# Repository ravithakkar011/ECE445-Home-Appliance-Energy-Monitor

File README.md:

# ECE445-Home-Appliance-Energy-Monitor

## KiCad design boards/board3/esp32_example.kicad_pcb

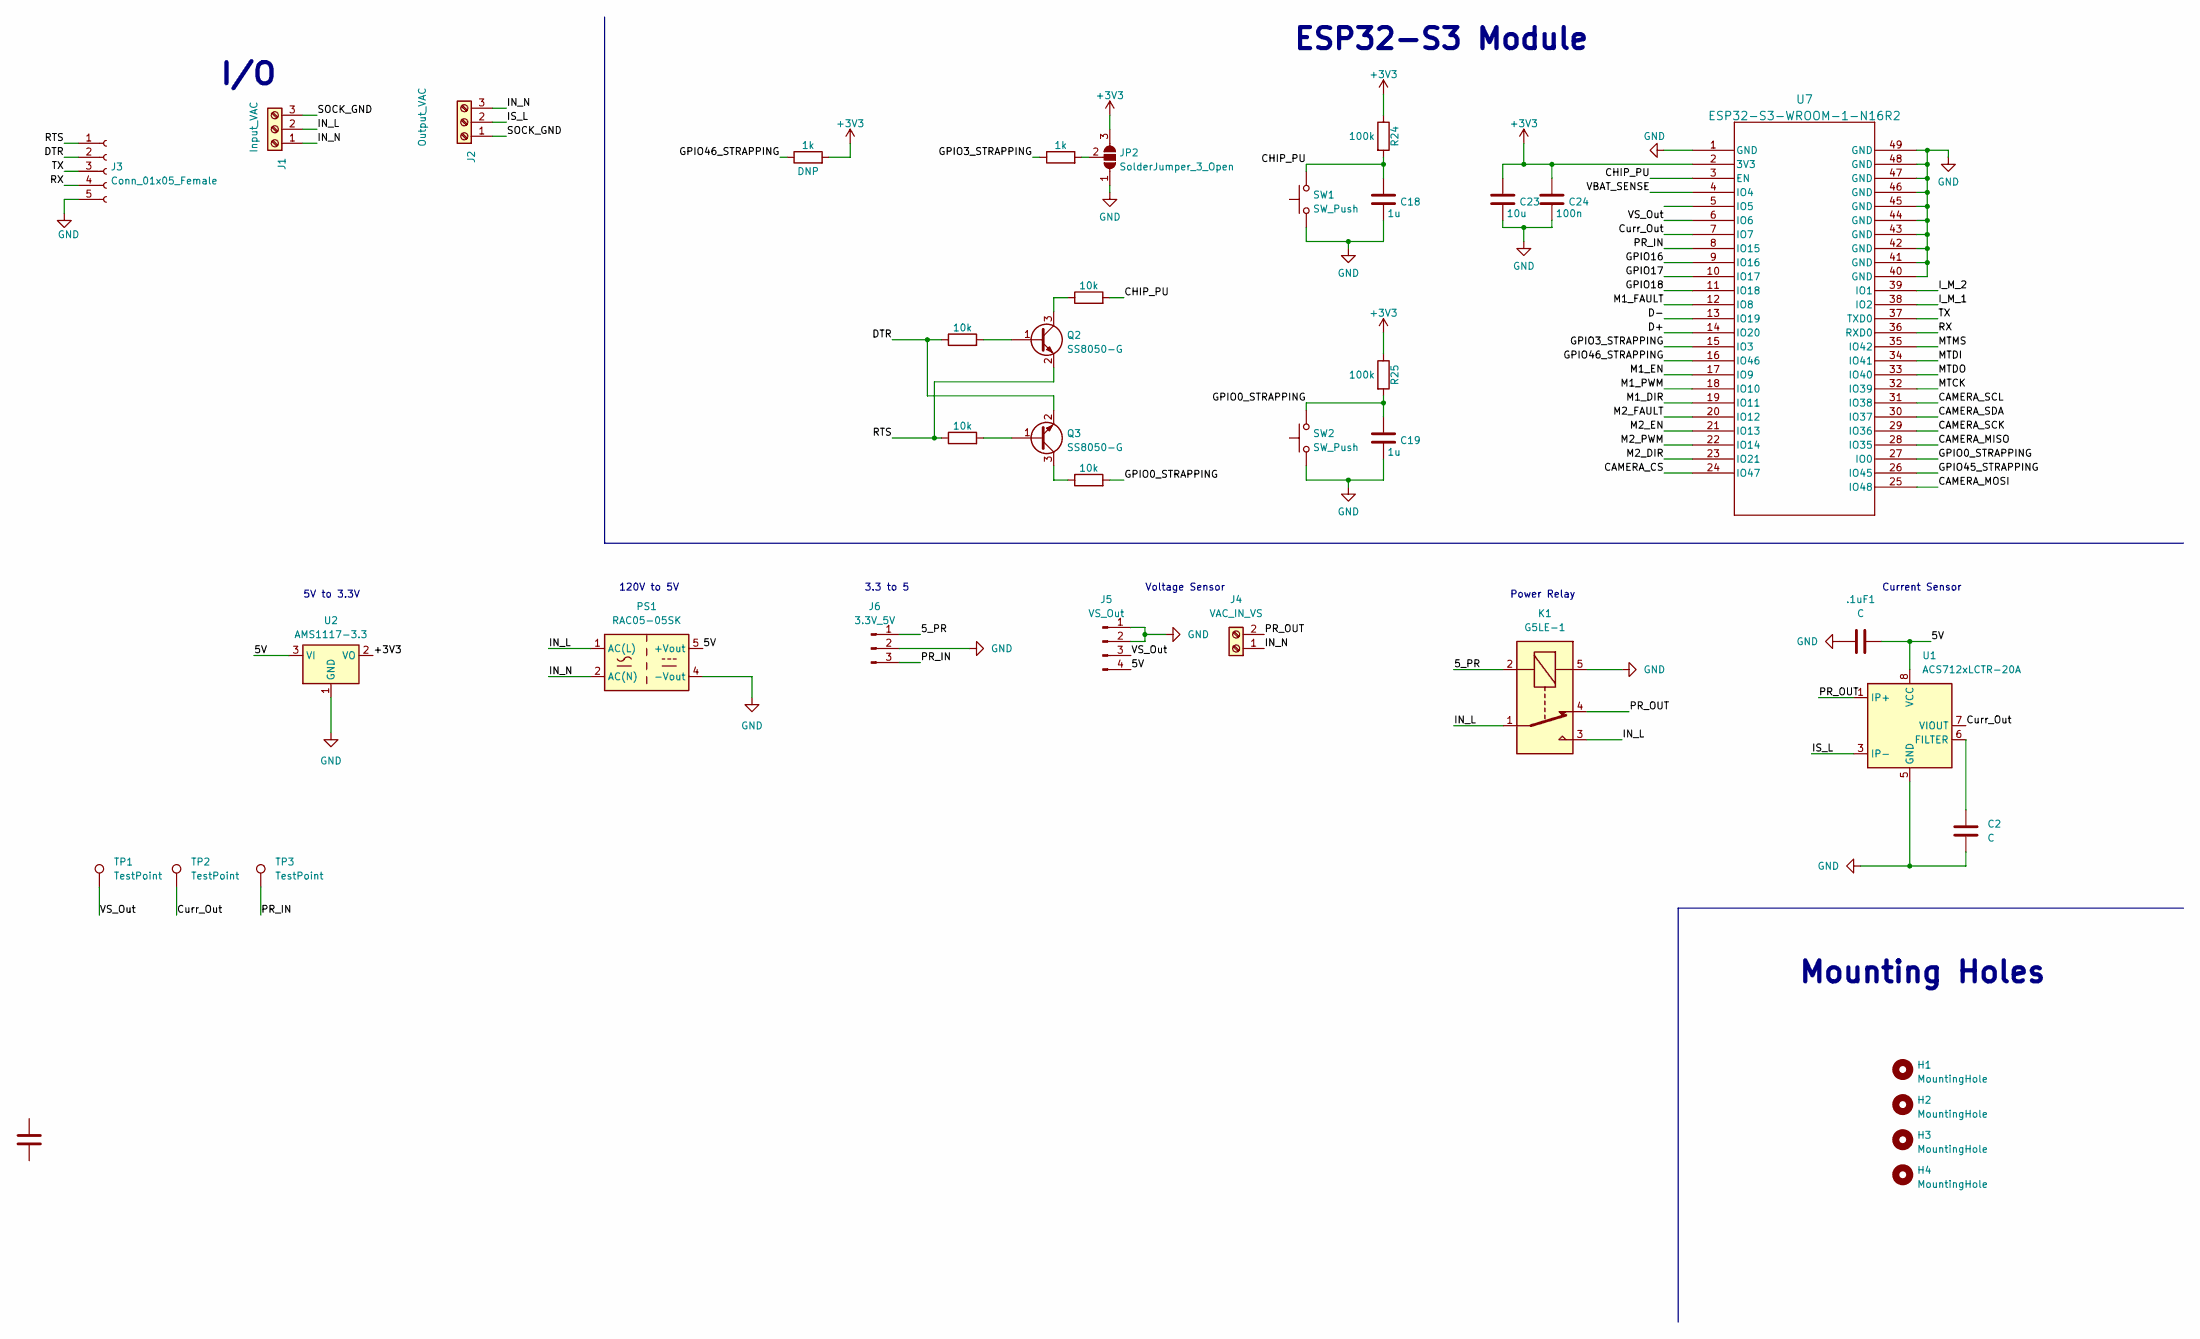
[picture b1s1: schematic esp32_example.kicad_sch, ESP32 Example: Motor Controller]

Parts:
.1uF1: C; C_0201_0603Metric
C1: 10u; R_1206_3216Metric
C2: C; C_0201_0603Metric
C18, C19: 1u; C_0805_2012Metric
C23: 10u; C_0805_2012Metric
C24: 100n; C_0805_2012Metric
H1, H2, H3, H4: MountingHole; MountingHole_3.2mm_M3
J1: Input_VAC; TerminalBlock_Phoenix_MKDS-1,5-3-5.08_1x03_P5.08mm_Horizont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
J2: Output_VAC; TerminalBlock_Phoenix_MKDS-1,5-3-5.08_1x03_P5.08mm_Horizont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
J3: Conn_01x05_Female; PinHeader_1x05_P2.54mm_Vertical
J4: VAC_IN_VS; TerminalBlock_Phoenix_MKDS-1,5-2_1x02_P5.00mm_Horizontal
J5: VS_Out; Molex_KK-254_AE-6410-04A_1x04_P2.54mm_Vertical
J6: 3.3V_5V; Molex_KK-254_AE-6410-03A_1x03_P2.54mm_Vertical
JP2: SolderJumper_3_Open; SolderJumper-3_P2.0mm_Open_TrianglePad1.0x1.5mm
K1: G5LE-1; Relay_SPDT_Omron-G5LE-1
PS1: RAC05-05SK; Converter_ACDC_RECOM_RAC05-xxSK_THT
Q2, Q3: SS8050-G; SOT-23
R12, R17: 1k; R_0805_2012Metric
R13, R14, R18, R19: 10k; R_0805_2012Metric
R24, R25: 100k; R_0805_2012Metric
SW1, SW2: SW_Push; SW_SPST_B3S-1000
TP1, TP2, TP3: TestPoint; TestPoint_Keystone_5010-5014_Multipurpose
U1: ACS712xLCTR-20A; SOIC-8_3.9x4.9mm_P1.27mm
U2: AMS1117-3.3; SOT-223-3_TabPin2
U7: ESP32-S3-WROOM-1-N16R2; ESP32-S3-WROOM-1_EXP

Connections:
+3V3: C23.1, C24.1, JP2.3 (B), R12.2, R24.1, R25.1, U2.2 (VO), U7.2 (3V3)
/5V: .1uF1.2, J5.4, PS1.5 (+Vout), U1.8 (VCC), U2.3 (VI)
/5_PR: J6.1, K1.2
/CAMERA_CS: U7.24 (IO47)
/CAMERA_MISO: U7.28 (IO35)
/CAMERA_MOSI: U7.25 (IO48)
/CAMERA_SCK: U7.29 (IO36)
/CAMERA_SCL: U7.31 (IO38)
/CAMERA_SDA: U7.30 (IO37)
/CHIP_PU: C18.1, R18.2, R24.2, SW1.2, U7.3 (EN)
/Curr_Out: TP2.1, U1.7 (VIOUT), U7.7 (IO7)
/D+: U7.14 (IO20)
/D-: U7.13 (IO19)
/DTR: J3.2, Q3.2 (E), R13.1
/GPIO0_STRAPPING: C19.1, R19.2, R25.2, SW2.2, U7.27 (IO0)
/GPIO3_STRAPPING: R17.1, U7.15 (IO3)
/GPIO16: U7.9 (IO16)
/GPIO17: U7.10 (IO17)
/GPIO18: U7.11 (IO18)
/GPIO45_STRAPPING: U7.26 (IO45)
/GPIO46_STRAPPING: R12.1, U7.16 (IO46)
/IN_L: J1.2, K1.1, K1.3, PS1.1 (AC(L))
/IN_N: J1.1, J2.3, J4.1, PS1.2 (AC(N))
/IS_L: J2.2, U1.3 (IP-), U1.4 (IP-)
/I_M_1: U7.38 (IO2)
/I_M_2: U7.39 (IO1)
/M1_DIR: U7.19 (IO11)
/M1_EN: U7.17 (IO9)
/M1_FAULT: U7.12 (IO8)
/M1_PWM: U7.18 (IO10)
/M2_DIR: U7.23 (IO21)
/M2_EN: U7.21 (IO13)
/M2_FAULT: U7.20 (IO12)
/M2_PWM: U7.22 (IO14)
/MTCK: U7.32 (IO39)
/MTDI: U7.34 (IO41)
/MTDO: U7.33 (IO40)
/MTMS: U7.35 (IO42)
/PR_IN: J6.3, TP3.1, U7.8 (IO15)
/PR_OUT: J4.2, K1.4, U1.1 (IP+), U1.2 (IP+)
/RTS: J3.1, Q2.2 (E), R14.1
/RX: J3.4, U7.36 (RXD0)
/SOCK_GND: J1.3, J2.1
/TX: J3.3, U7.37 (TXD0)
/VBAT_SENSE: U7.4 (IO4)
/VS_Out: J5.3, TP1.1, U7.6 (IO6)
GND: .1uF1.1, C2.2, C18.2, C19.2, C23.2, C24.2, J3.5, J5.1, J5.2, J6.2, JP2.1 (A), K1.5, PS1.4 (-Vout), SW1.1, SW2.1, U1.5 (GND), U2.1 (GND), U7.1 (GND), U7.40 (GND), U7.41 (GND), U7.42 (GND), U7.43 (GND), U7.44 (GND), U7.45 (GND), U7.46 (GND), U7.47 (GND), U7.48 (GND), U7.49 (GND)
unnamed: JP2.2 (C), R17.2
unnamed: Q2.1 (B), R13.2
unnamed: Q2.3 (C), R18.1
unnamed: Q3.1 (B), R14.2
unnamed: Q3.3 (C), R19.1
unnamed: C2.1, U1.6 (FILTER)

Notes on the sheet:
Voltage Sensor
3.3 to 5
Current Sensor
120V to 5V
ESP32-S3 Module
Mounting Holes
5V to 3.3V
Power Relay
I/O

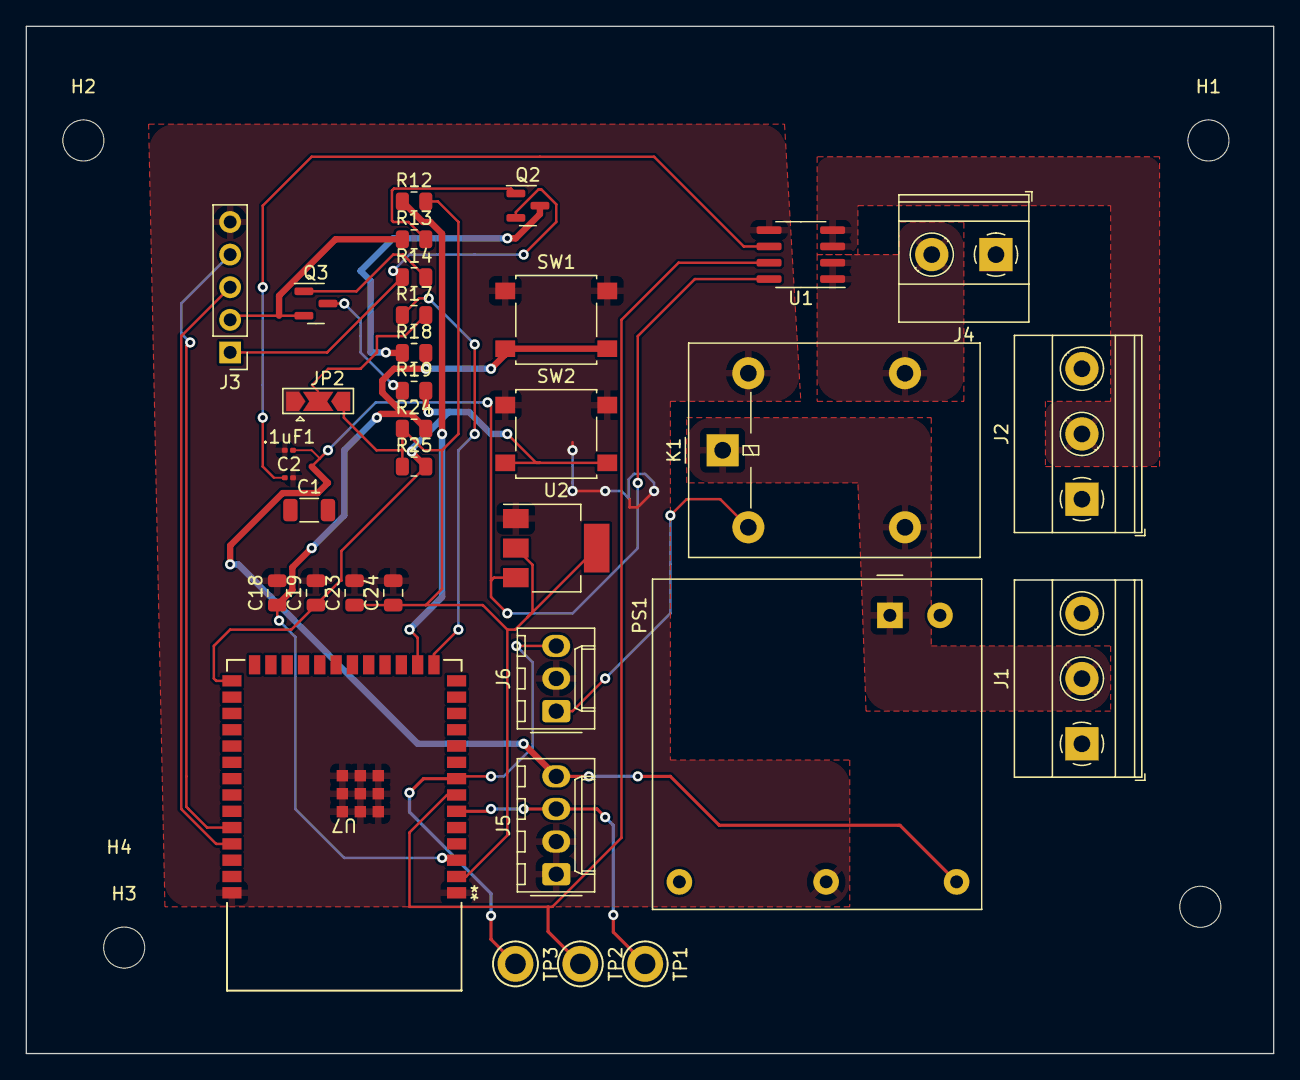
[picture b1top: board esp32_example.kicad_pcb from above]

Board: 2 copper layers, 97.2 x 80.0 mm, 38 parts (0 on the bottom side), 26 nets.

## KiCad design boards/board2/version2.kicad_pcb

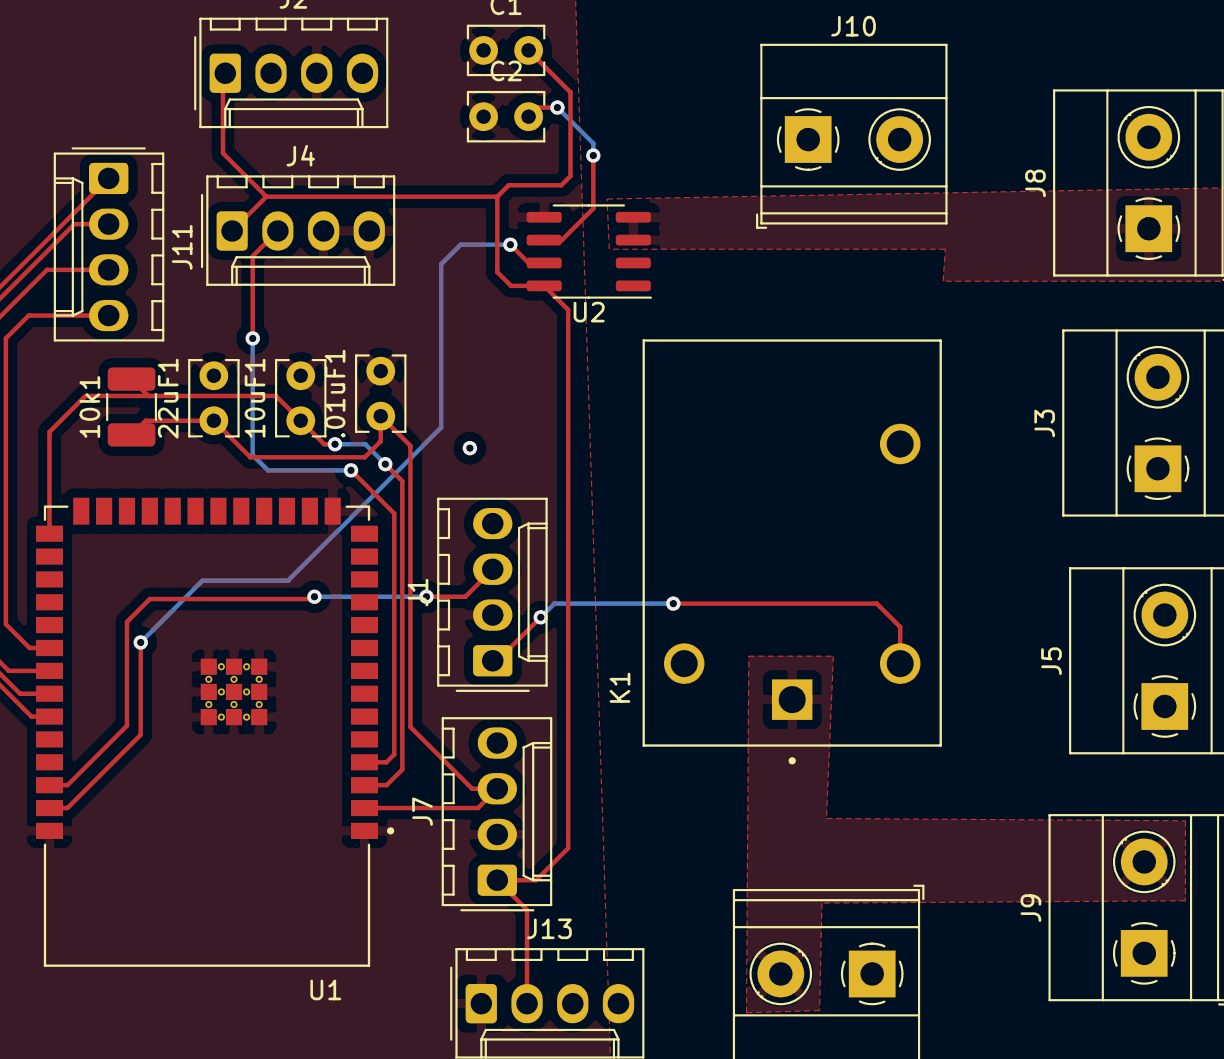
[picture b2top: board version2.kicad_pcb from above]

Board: 2 copper layers, 21 parts (0 on the bottom side), 18 nets.

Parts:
10k1: R; R_1210_3225Metric_Pad1.30x2.65mm_HandSolder
10uF1, 22uF1, .01uF1: C; C_Rect_L4.0mm_W2.5mm_P2.50mm
C1, C2: C; C_Rect_L4.0mm_W2.5mm_P2.50mm
J1: 3.3_5_boost; Molex_KK-254_AE-6410-04A_1x04_P2.54mm_Vertical
J2: Scopy Connection; Molex_KK-254_AE-6410-04A_1x04_P2.54mm_Vertical
J3: SecondOutGND; TerminalBlock_Phoenix_MKDS-1,5-2-5.08_1x02_P5.08mm_Horizont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
J4: Voltage_Sensor; Molex_KK-254_AE-6410-04A_1x04_P2.54mm_Vertical
J5: SecondGNDPin; TerminalBlock_Phoenix_MKDS-1,5-2-5.08_1x02_P5.08mm_Horizont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
J7: 5_3_connector; Molex_KK-254_AE-6410-04A_1x04_P2.54mm_Vertical
J8: OutVAC; TerminalBlock_Phoenix_MKDS-1,5-2-5.08_1x02_P5.08mm_Horizont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
J9: MainPin; TerminalBlock_Phoenix_MKDS-1,5-2-5.08_1x02_P5.08mm_Horizont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
J10: Voltage_Sensor_Input; TerminalBlock_Phoenix_MKDS-1,5-2-5.08_1x02_P5.08mm_Horizont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
J11: JTAG; Molex_KK-254_AE-6410-04A_1x04_P2.54mm_Vertical
J13: OutPut and Ground; Molex_KK-254_AE-6410-04A_1x04_P2.54mm_Vertical
J14: VAC Conn; TerminalBlock_Phoenix_MKDS-1,5-2-5.08_1x02_P5.08mm_Horizont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
K1: G5LE-1A; RELAY_G5LE-1A-EDC5
U1: ESP32-S3-WROOM-1-N16R2; XCVR_ESP32-S3-WROOM-1-N16R2
U2: ACS712xLCTR-20A; SOIC-8_3.9x4.9mm_P1.27mm

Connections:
GND: 10uF1.2, 22uF1.2, .01uF1.2, C1.1, C2.1, J1.2, J2.3, J4.3, J4.4, J7.2, J13.1, K1.5, U1.1, U1.15, U1.40, U1.41_1, U1.41_2, U1.41_3, U1.41_4, U1.41_5, U1.41_6, U1.41_7, U1.41_8, U1.41_9, U2.5
unnamed: 10k1.2, 10uF1.1, U1.3, U1.27
unnamed: 10k1.1, 22uF1.1, .01uF1.1, J7.3, U1.2
unnamed: C1.2, J2.1, J4.1, J7.1, J13.2, U2.8
unnamed: C2.2, U2.6
unnamed: J1.1, K1.2
unnamed: J1.3, U1.38
unnamed: J3.2, J5.1
unnamed: J4.2, U1.4
unnamed: J8.1, U2.3, U2.4
unnamed: J10.1, K1.3, U2.1, U2.2
unnamed: J8.2, J9.1, J10.2, J14.1
unnamed: J11.1, U1.35
unnamed: J11.2, U1.34
unnamed: J11.3, U1.33
unnamed: J11.4, U1.32
unnamed: J9.2, J14.2, K1.1
unnamed: U1.39, U2.7

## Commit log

2023-09-12 added directories and readmes
2023-10-25 PCB design 2
2023-11-29 working copy of the esp controller application
2023-12-07 Create 8-28-23 Team Meeting
2023-12-07 Create 8-31-23
2023-12-07 Rename 8-31-23 to 8-31-23 Team Meeting
2023-12-07 Create 9-5-23 Team Meeting
2023-12-07 Create 9-12-23 Team Meeting
2023-12-07 Rename 8-28-23 Team Meeting to 1. 8-28-23 Team Meeting
2023-12-07 Rename 8-31-23 Team Meeting to 2. 8-31-23 Team Meeting
2023-12-07 Rename 9-1-23 Initial Design.pdf to 3. 9-1-23 Initial Design.pdf
2023-12-07 Rename 9-5-23 Team Meeting to 4. 9-5-23 Team Meeting
2023-12-07 Rename 9-7-23 Team Meeting.pdf to 5. 9-7-23 Team Meeting.pdf
2023-12-07 Rename 9-12-23 Team Meeting to 6. 9-12-23 Team Meeting
2023-12-07 Update 6. 9-12-23 Team Meeting
2023-12-07 Create 7. 9-14-23 Team Meeting
2023-12-07 Create 8-28-23TeamMeeting
2023-12-07 Update 8-28-23TeamMeeting
2023-12-07 Create 8. 9-15-23 Team Meeting
2023-12-07 added more to my notebook
2023-12-07 Pushing notebook stuff
2023-12-07 Rename 9-19-23 Team Meeting.pdf to 9. 9-19-23 Team Meeting.pdf
2023-12-07 Create 8-31-23Meeting
2023-12-07 Rename 10. 9-21-23 Team Meeting.pdf to 10. 9-21-23 Team Meeting.pdf
2023-12-07 Rename 10. 9-21-23 Team Meeting.pdf to 10. 9-21-23 Team Meeting.pdf
2023-12-07 Rename 1. 8-28-23 Team Meeting to 1. 8-28-23 Team Meeting
2023-12-07 Rename 2. 8-31-23 Team Meeting to 2. 8-31-23 Team Meeting
2023-12-07 Rename 3. 9-1-23 Initial Design.pdf to 3. 9-1-23 Initial Design.pdf
2023-12-07 Rename 4. 9-5-23 Team Meeting to 4. 9-5-23 Team Meeting
2023-12-07 Rename 5. 9-7-23 Team Meeting.pdf to 5. 9-7-23 Team Meeting.pdf
2023-12-07 Rename 6. 9-12-23 Team Meeting to 6. 9-12-23 Team Meeting
2023-12-07 Rename 7. 9-14-23 Team Meeting to 7. 9-14-23 Team Meeting
2023-12-07 Rename 8. 9-15-23 Team Meeting to 8. 9-15-23 Team Meeting
2023-12-07 Rename 9. 9-19-23 Team Meeting.pdf to 9. 9-19-23 Team Meeting.pdf
2023-12-07 added more files
2023-12-07 Create 9-1-2023Meeting
2023-12-07 Create 11. 9-27-23 Team Meeting
2023-12-07 Update and rename 11. 9-27-23 Team Meeting to 11. 9-28-23 Team Meeting
2023-12-08 Create 12. 9-30-23 Individual Work
2023-12-08 Create 9-5-2023Meeting
2023-12-08 Create 13. 10-4-23 Design Review
2023-12-08 Create 14. 10-7-23 PCB Review
2023-12-08 Create 9-7-2023Meeting
2023-12-08 Update 13. 10-4-23 Design Review
2023-12-08 Create 15. 10-11-23 Individual Work
2023-12-08 Create 16. 10-16-23 PCB Review
2023-12-08 Create 17. 10-20-16 Team Meeting
2023-12-08 Create 18. 10-25-23
2023-12-08 Rename 18. 10-25-23 to 18. 10-25-23 Individual Work
2023-12-08 Create 19. 10-31-23 Individual Work
2023-12-08 Added more notes
2023-12-08 Create 20. 11-9-23 Team Meeting
2023-12-08 Update 20. 11-9-23 Team Meeting
2023-12-08 forgot to add notes
2023-12-08 Create 21. 11-13-23 PCB Soldering
2023-12-08 Create 22. 11-14-23 Soldering
2023-12-08 Update 15. 10-11-23 Individual Work
2023-12-08 Update 22. 11-14-23 Soldering
2023-12-08 Create 23. 11-16-23 Mock Demo
2023-12-08 Update 23. 11-16-23 Mock Demo
2023-12-08 Create 24. Fall Break
2023-12-08 Create 25. 11-27-23
2023-12-08 Rename 25. 11-27-23 to 25. 11-27-23 Sensor Testing
2023-12-08 Create 26. 11-28-23 Power Relay Testing
2023-12-08 Create 27. 11-29-23 Team Meeting
2023-12-08 Update and rename 27. 11-29-23 Team Meeting to 28. 11-30-23 Team Meeting
2023-12-08 Create 27. 11-29-23 Final Demo
2023-12-08 Create 29. 12-1-23 Mock Presentation
2023-12-08 Create 30. 12-2-23 Final Testing
2023-12-08 Create 31. 12-5-23 Final Presentation
2023-12-08 Create 9-12-2023Meeting
2023-12-08 Create 9-14-23Meeting
2023-12-08 adding more notebook entries
2023-12-08 Create 9-15-2023Meeting
2023-12-08 Create 9-19-2023Meeting
2023-12-08 Create 9-21-2023Meeting
2023-12-08 Create 9-28-23Meeting
2023-12-08 Create 10-12-2023IndWork
2023-12-08 Create 10-20-2023Meeting
2023-12-08 Create 10-28-2023IndWork
2023-12-08 Create 11-9-2023TeamMeeting
2023-12-08 Create 11-16-2023MockDemo
2023-12-08 Create FallBreakWork
2023-12-08 Create 11-27-2023SensorTesting
2023-12-08 Create 11-28-2023PowerRelayWork
2023-12-08 Create FinalDemo
2023-12-08 Create 11-30-23Team Meeting
2023-12-08 Create MockPresentation
2023-12-08 Create TestingWithNewSensor
2023-12-08 Create FinalPresentation
2023-12-08 Create ProjectVideo
